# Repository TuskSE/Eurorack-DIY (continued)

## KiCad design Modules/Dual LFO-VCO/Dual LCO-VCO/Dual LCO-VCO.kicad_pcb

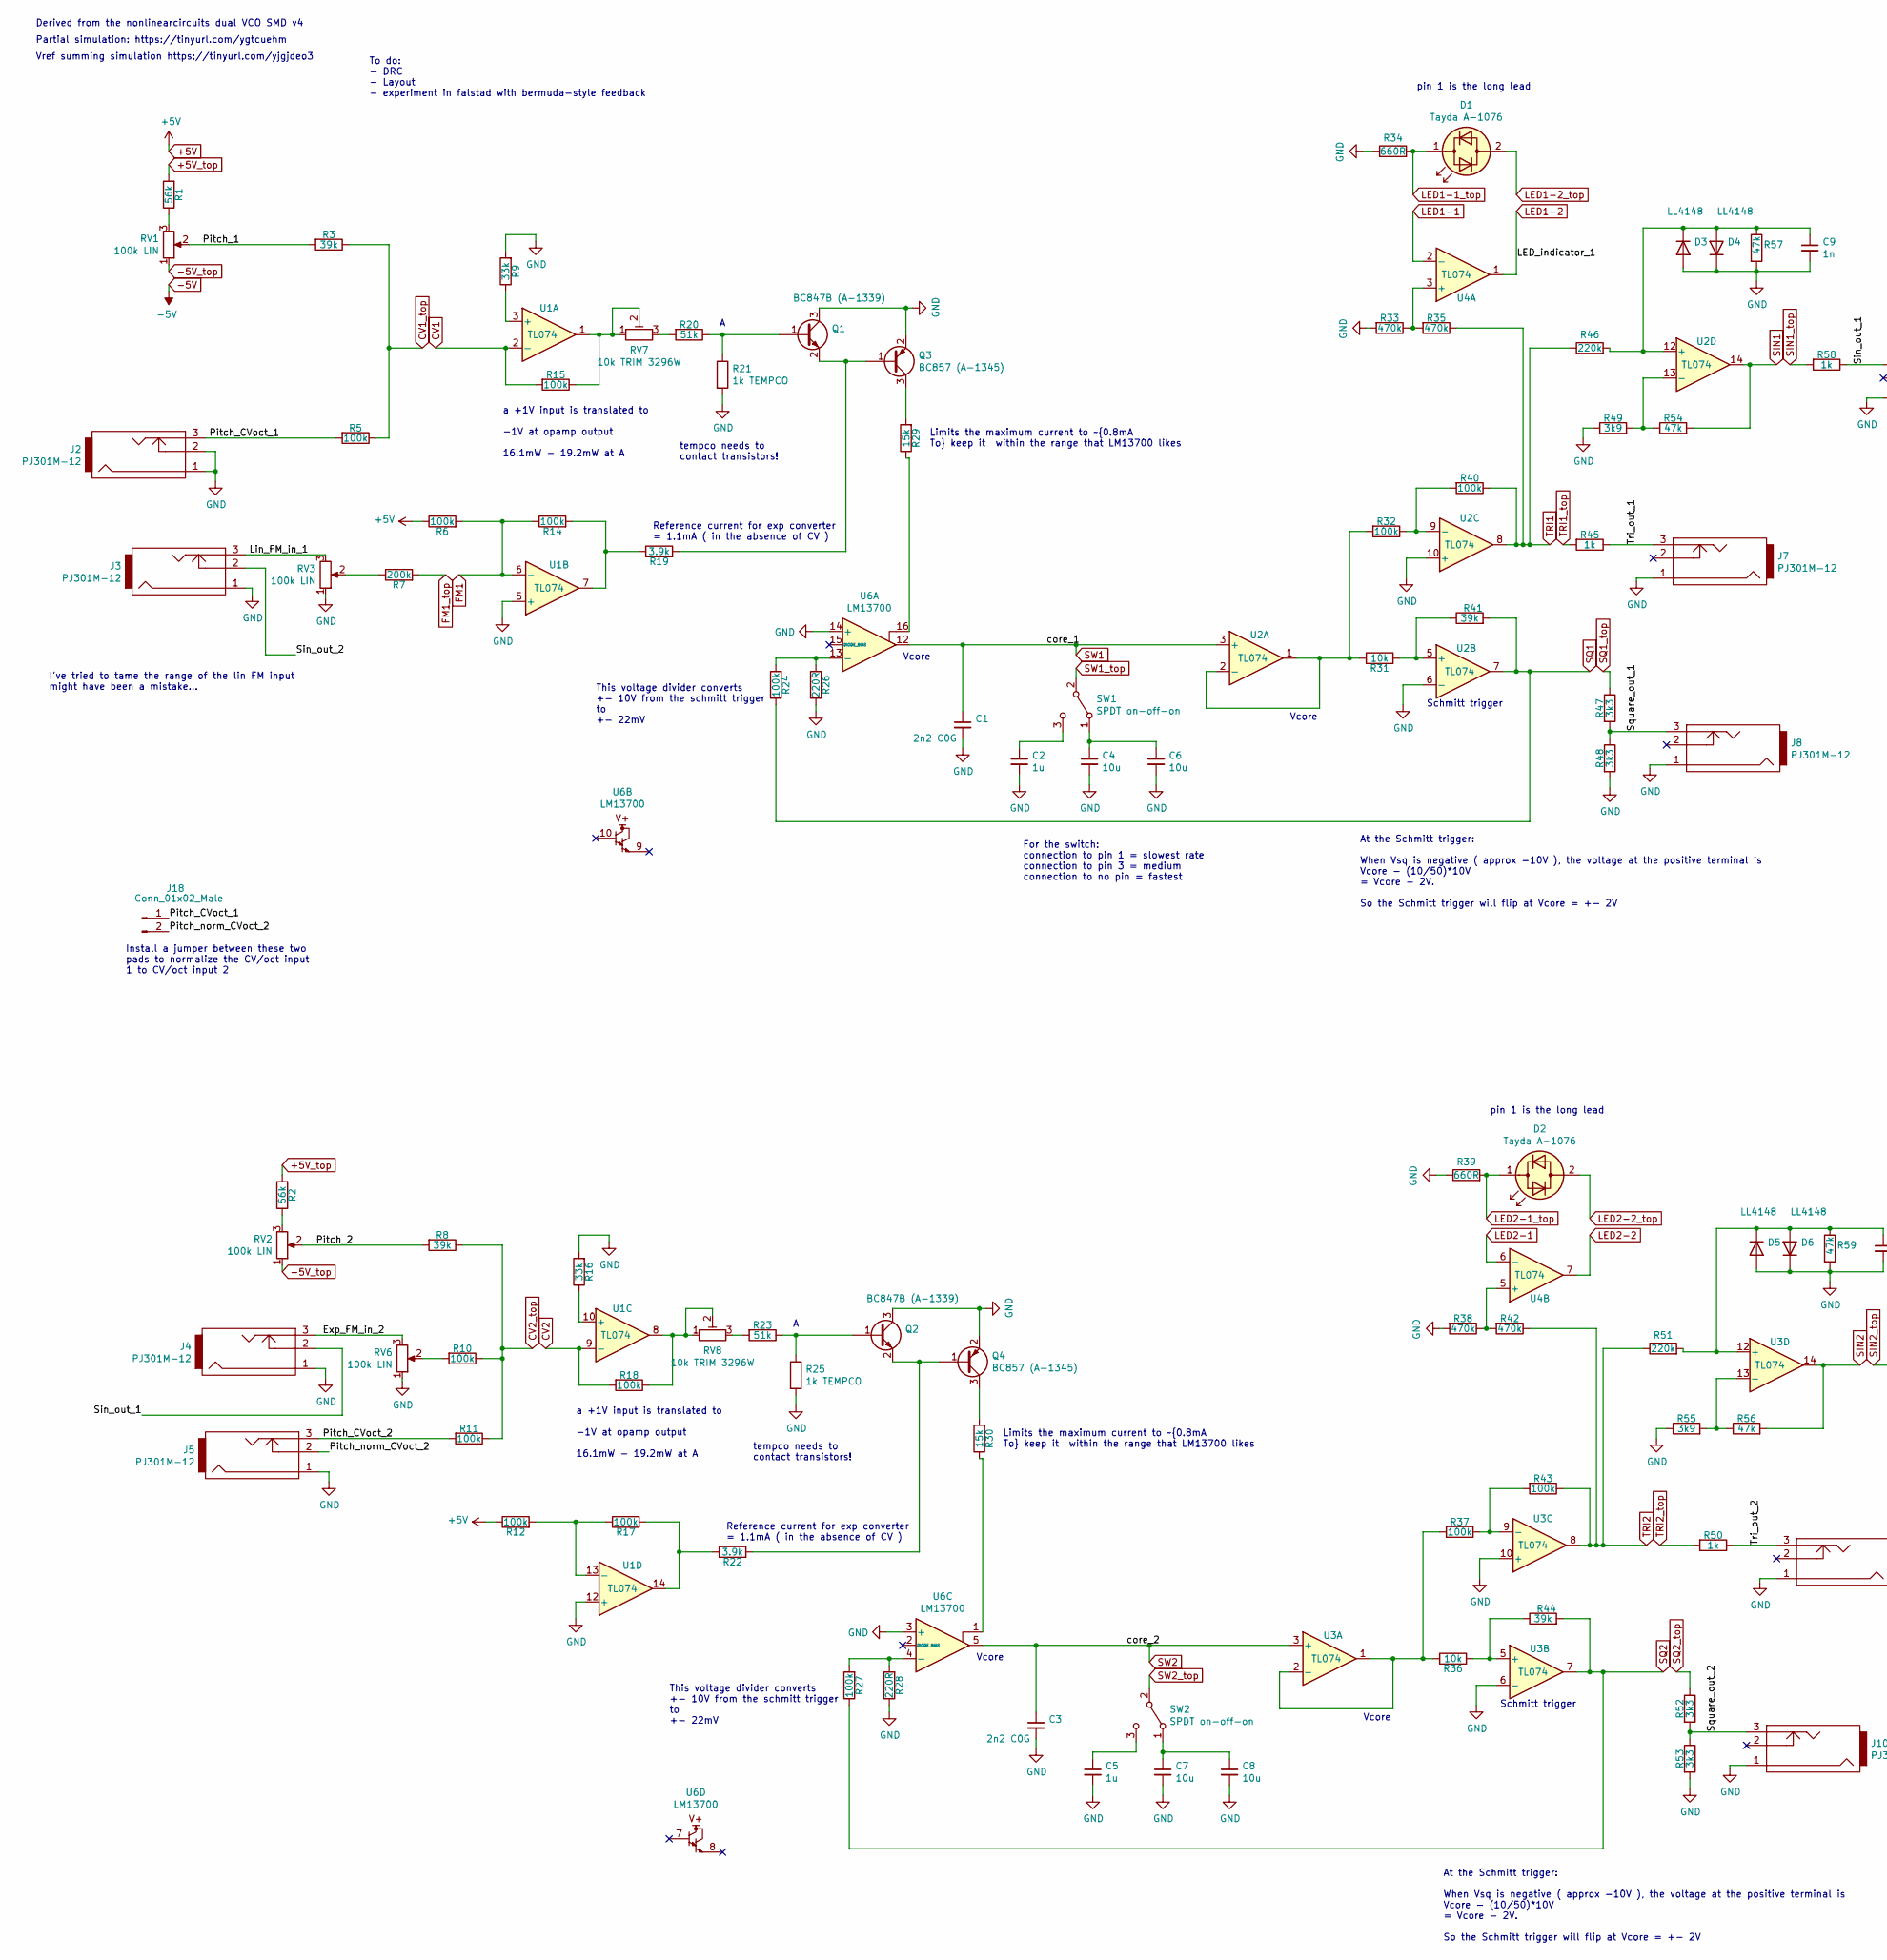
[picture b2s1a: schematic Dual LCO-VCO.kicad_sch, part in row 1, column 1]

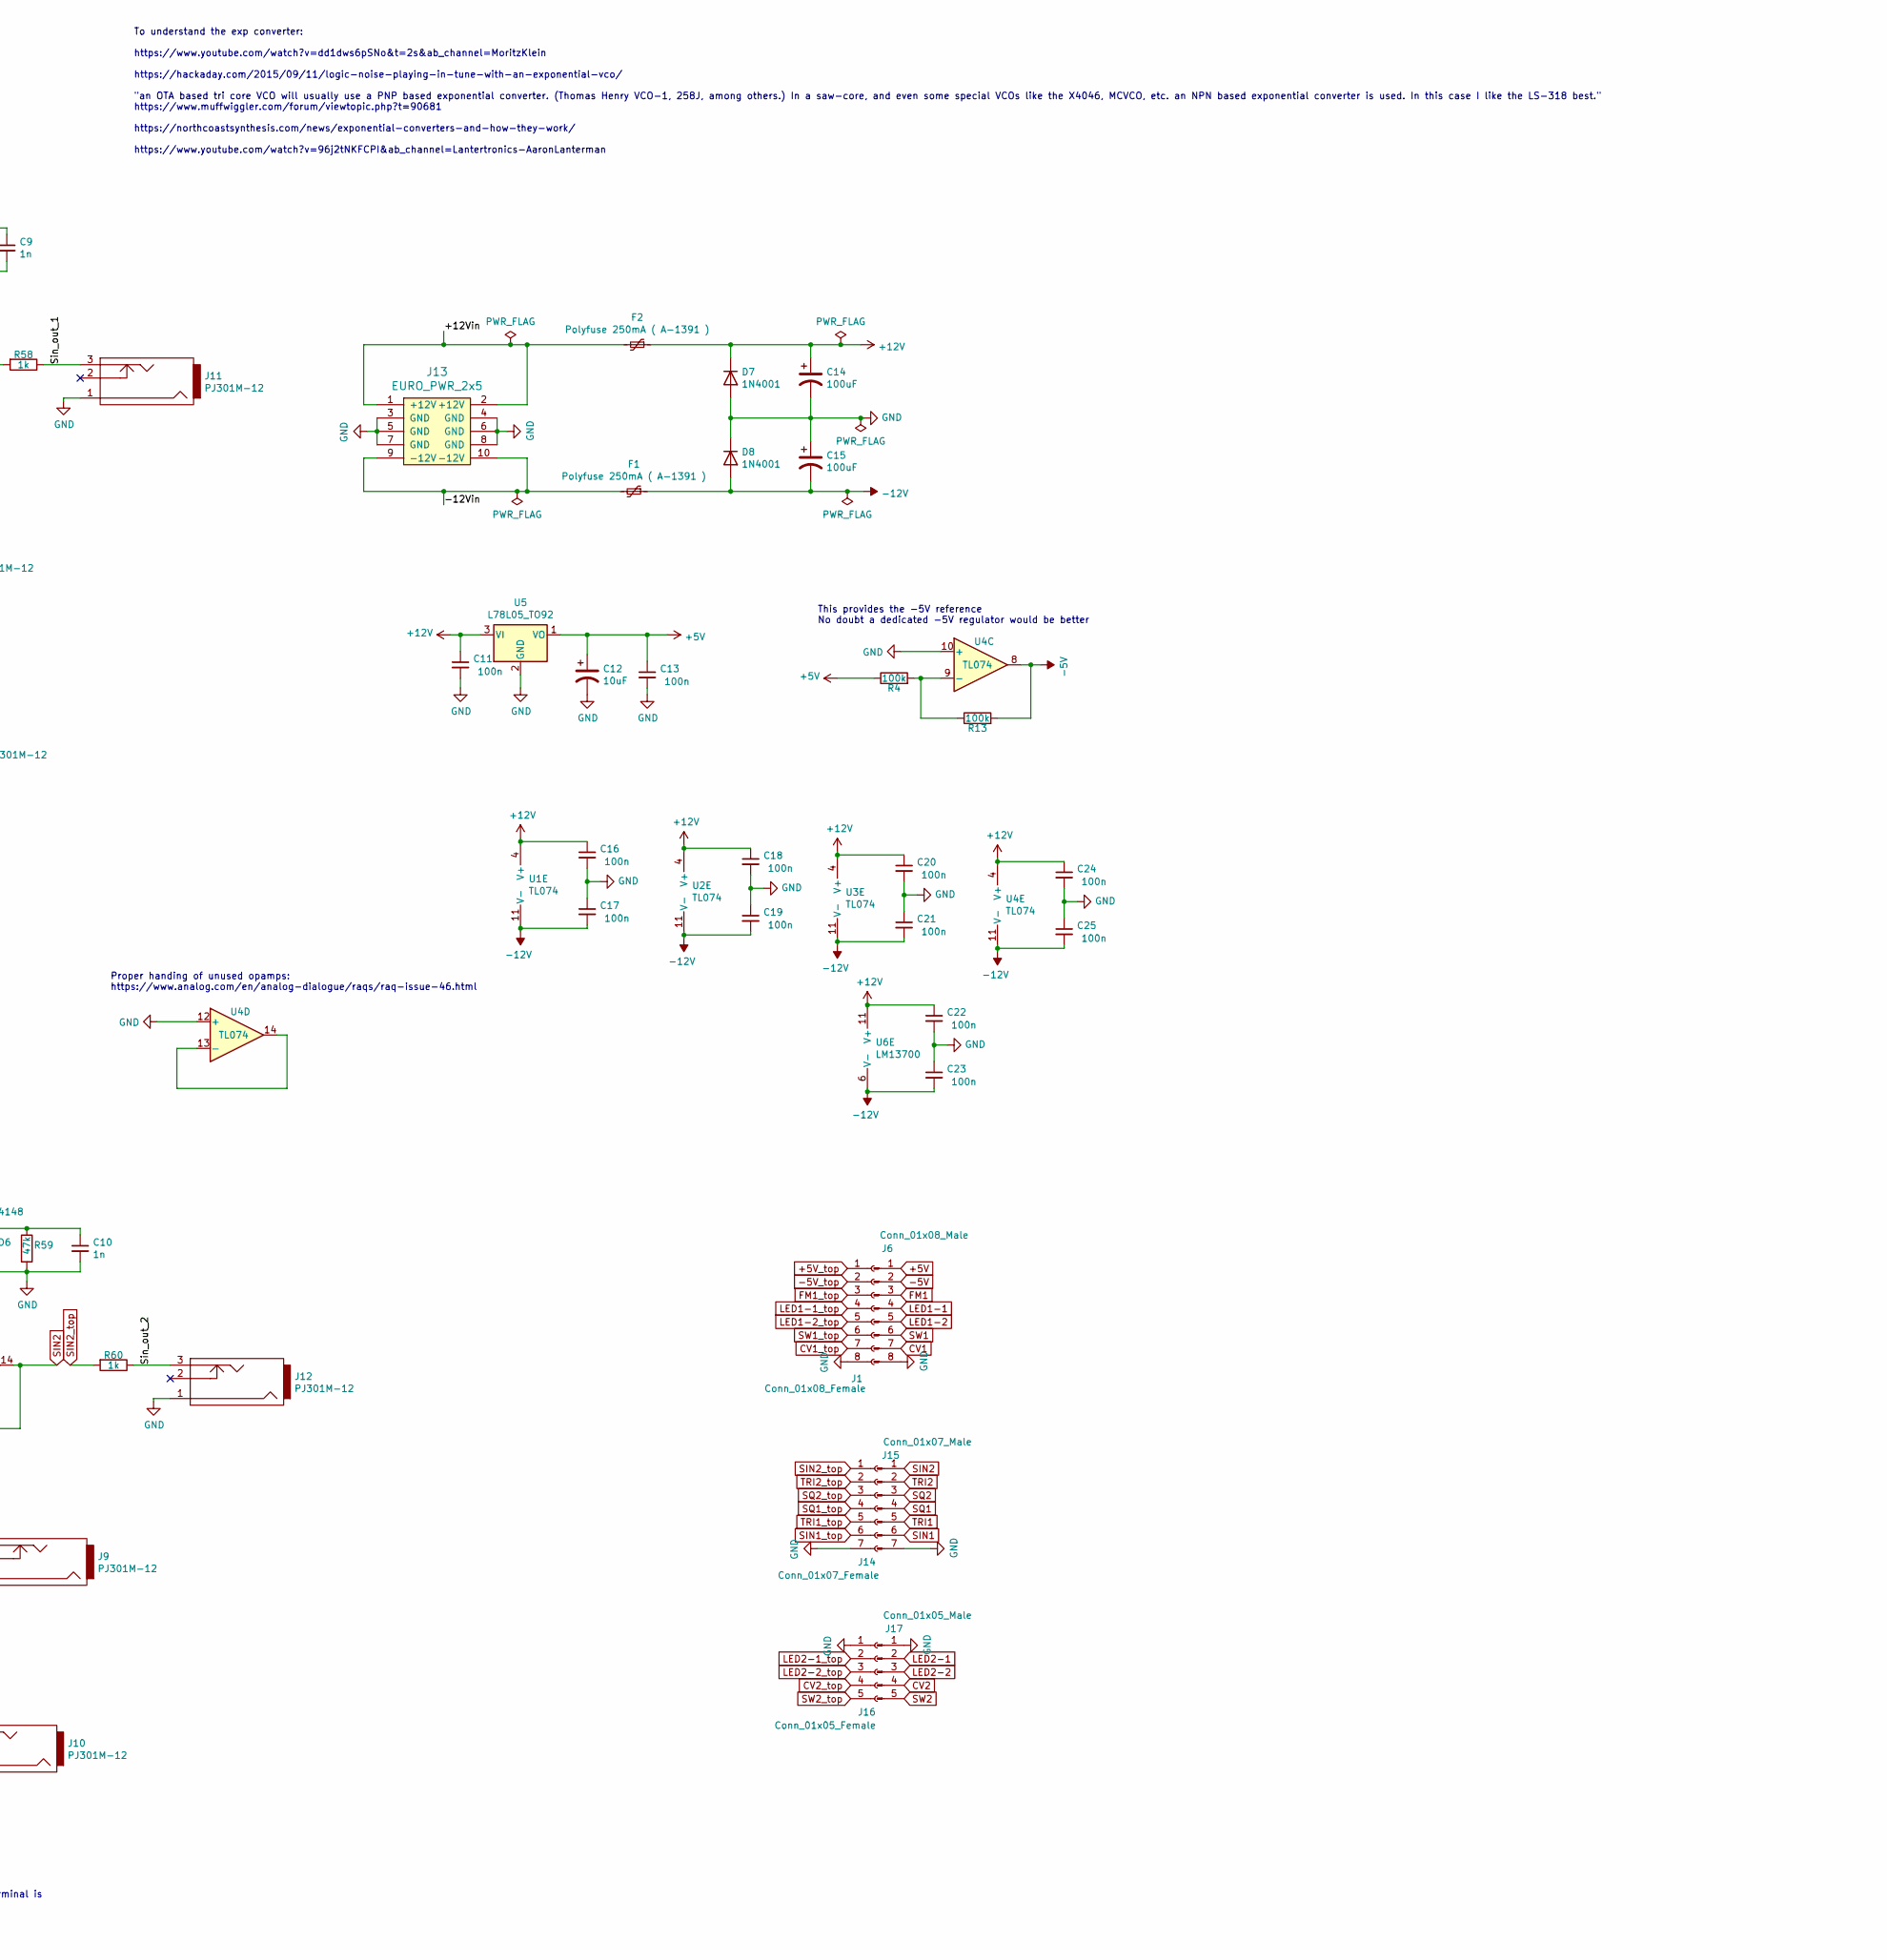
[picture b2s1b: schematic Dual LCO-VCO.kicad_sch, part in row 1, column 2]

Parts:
C1, C3: 2n2 C0G; C_0603_1608Metric_Pad1.05x0.95mm_HandSolder
C2, C5: 1u; C_0805_2012Metric_Pad1.15x1.40mm_HandSolder_smallText
C4, C6, C7, C8: 10u; C_0805_2012Metric_Pad1.15x1.40mm_HandSolder_smallText
C9, C10: 1n; C_0805_2012Metric_Pad1.15x1.40mm_HandSolder_SmallTxt
C11, C13, C16, C17, C18, C19, C20, C21, C22, C23, C24, C25: 100n; C_0805_2012Metric_Pad1.15x1.40mm_HandSolder_SmallTxt
C12: 10uF; CP_Radial_D6.3mm_P2.50mm
C14, C15: 100uF; CP_Radial_D6.3mm_P2.50mm
D1, D2: Tayda A-1076; LED3mm
D3, D4, D5, D6: LL4148; D_MiniMELF
D7, D8: 1N4001; D_DO-41_SOD81_P10.16mm_Horizontal
F1, F2: Polyfuse 250mA ( A-1391 ); C_Disc_D7.5mm_W2.5mm_P5.00mm
J1: Conn_01x08_Female; PinHeader_1x08_P2.54mm_Vertical
J2, J3, J4, J5, J7, J8, J9, J10, J11, J12: PJ301M-12; PJ301M-12_Compact
J6: Conn_01x08_Male; PinHeader_1x08_P2.54mm_Vertical
J13: EURO_PWR_2x5; Eurorack_power_header
J14: Conn_01x07_Female; PinHeader_1x07_P2.54mm_Vertical
J15: Conn_01x07_Male; PinHeader_1x07_P2.54mm_Vertical
J16: Conn_01x05_Female; PinHeader_1x05_P2.54mm_Vertical
J17: Conn_01x05_Male; PinHeader_1x05_P2.54mm_Vertical
J18: Conn_01x02_Male; PinHeader_1x02_P2.54mm_Vertical
Q1, Q2: BC847B (A-1339); SOT-23
Q3, Q4: BC857 (A-1345); SOT-23
R1, R2: 56k; R_0805_2012Metric_Pad1.15x1.40mm_HandSolder_smallText
R3, R8, R41, R44: 39k; R_0805_2012Metric_Pad1.15x1.40mm_HandSolder_smallText
R4, R5, R6, R10, R11, R12, R13, R14, R15, R17, R18, R24, R27, R32, R37, R40, R43: 100k; R_0805_2012Metric_Pad1.15x1.40mm_HandSolder_smallText
R7: 200k; R_0805_2012Metric_Pad1.15x1.40mm_HandSolder_smallText
R9, R16: 33k; R_0805_2012Metric_Pad1.15x1.40mm_HandSolder_smallText
R19, R22: 3.9k; R_0805_2012Metric_Pad1.15x1.40mm_HandSolder_smallText
R20, R23: 51k; R_0805_2012Metric_Pad1.15x1.40mm_HandSolder_smallText
R21, R25: 1k TEMPCO; R_Axial_DIN0414_L11.9mm_D4.5mm_P25.40mm_Horizontal
R26, R28: 220R; R_0805_2012Metric_Pad1.15x1.40mm_HandSolder_smallText
R29, R30: 15k; R_0805_2012Metric_Pad1.15x1.40mm_HandSolder_smallText
R31, R36: 10k; R_0805_2012Metric_Pad1.15x1.40mm_HandSolder_smallText
R33, R35, R38, R42: 470k; R_0805_2012Metric_Pad1.15x1.40mm_HandSolder_smallText
R34, R39: 660R; R_0805_2012Metric_Pad1.15x1.40mm_HandSolder_smallText
R45, R50, R58, R60: 1k; R_0805_2012Metric_Pad1.15x1.40mm_HandSolder_smallText
R46, R51: 220k; R_0805_2012Metric_Pad1.15x1.40mm_HandSolder_smallText
R47, R48, R52, R53: 3k3; R_0805_2012Metric_Pad1.15x1.40mm_HandSolder_smallText
R49, R55: 3k9; R_0805_2012Metric_Pad1.15x1.40mm_HandSolder_smallText
R54, R56, R57, R59: 47k; R_0805_2012Metric_Pad1.15x1.40mm_HandSolder_smallText
RV1, RV2, RV3, RV6: 100k LIN; Alpha9mmPot
RV7, RV8: 10k TRIM 3296W; Potentiometer_Bourns_3296W_Vertical
SW1, SW2: SPDT on-off-on; SPDT toggle on-off-on
U1, U2, U3, U4: TL074; SOIC-14_3.9x8.7mm_P1.27mm
U5: L78L05_TO92; TO-92_HandSolder
U6: LM13700; SOIC-16_3.9x9.9mm_P1.27mm

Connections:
+5V: C12.1, C13.1, J6.1, R4.1, R6.1, R12.1, U5.1 (VO)
+5V_top: J1.1, R1.2, R2.2
+12V: C11.1, C14.1, C16.1, C18.1, C20.1, C22.1, C24.1, D7.1 (K), F2.1, U1.4 (V+), U2.4 (V+), U3.4 (V+), U4.4 (V+), U5.3 (VI), U6.11 (V+)
-5V: J6.2, R13.2, U4.8
-5V_top: J1.2, RV1.1, RV2.1
-12V: C15.2, C17.2, C19.2, C21.2, C23.2, C25.2, D8.2 (A), F1.1, U1.11 (V-), U2.11 (V-), U3.11 (V-), U4.11 (V-), U6.6 (V-)
/+12Vin: F2.2, J13.1 (+12V), J13.2 (+12V)
/-12Vin: F1.2, J13.9 (-12V), J13.10 (-12V)
/Exp_FM_in_2: J4.3, RV6.3
/Lin_FM_in_1: J3.3, RV3.3
/Pitch_1: R3.2, RV1.2
/Pitch_2: R8.2, RV2.2
/Pitch_CVoct_1: J2.3, J18.1, R5.2
/Pitch_CVoct_2: J5.3, R11.2
/Pitch_norm_CVoct_2: J5.2, J18.2
/Sin_out_1: J4.2, J11.3, R58.1
/Sin_out_2: J3.2, J12.3, R60.1
/Square_out_1: J8.3, R47.2, R48.1
/Square_out_2: J10.3, R52.2, R53.1
/Tri_out_1: J7.3, R45.1
/Tri_out_2: J9.3, R50.1
CV1: J6.7, R15.2, U1.2 (-)
CV1_top: J1.7, R3.1, R5.1
CV2: J17.4, R18.2, U1.9 (-)
CV2_top: J16.4, R8.1, R10.1, R11.1
FM1: J6.3, R6.2, R14.1, U1.6 (-)
FM1_top: J1.3, R7.2
GND: C1.2, C2.2, C3.2, C4.2, C5.2, C6.2, C7.2, C8.2, C9.2, C10.2, C11.2, C12.2, C13.2, C14.2, C15.1, C16.2, C17.1, C18.2, C19.1, C20.2, C21.1, C22.2, C23.1, C24.2, C25.1, D3.2 (A), D4.1 (K), D5.2 (A), D6.1 (K), D7.2 (A), D8.1 (K), J1.8, J2.1, J2.2, J3.1, J4.1, J5.1, J6.8, J7.1, J8.1, J9.1, J10.1, J11.1, J12.1, J13.3 (GND), J13.4 (GND), J13.5 (GND), J13.6 (GND), J13.7 (GND), J13.8 (GND), J14.7, J15.7, J16.1, J17.1, Q1.3 (C), Q2.3 (C), Q3.2 (E), Q4.2 (E), R9.2, R16.2, R21.2, R25.2, R26.1, R28.1, R33.2, R34.1, R38.2, R39.1, R48.2, R49.1, R53.2, R55.1, R57.2, R59.2, RV3.1, RV6.1, U1.5 (+), U1.12 (+), U2.6 (-), U2.10 (+), U3.6 (-), U3.10 (+), U4.10 (+), U4.12 (+), U5.2 (GND), U6.3 (+), U6.14 (+)
LED1-1: J6.4, U4.2 (-)
LED1-1_top: D1.1 (KA), J1.4, R34.2
LED1-2: J6.5, U4.1
LED1-2_top: D1.2 (AK), J1.5
LED2-1: J17.2, U4.6 (-)
LED2-1_top: D2.1 (KA), J16.2, R39.2
LED2-2: J17.3, U4.7
LED2-2_top: D2.2 (AK), J16.3
unnamed: C2.1, SW1.3 (C)
unnamed: C4.1, C6.1, SW1.1 (A)
unnamed: C5.1, SW2.3 (C)
unnamed: C7.1, C8.1, SW2.1 (A)
unnamed: C9.1, D3.1 (K), D4.2 (A), R46.2, R57.1, U2.12 (+)
unnamed: C10.1, D5.1 (K), D6.2 (A), R51.2, R59.1, U3.12 (+)
unnamed: Q1.1 (B), R20.1, R21.1
unnamed: Q1.2 (E), Q3.1 (B), R19.2
unnamed: Q2.1 (B), R23.1, R25.1
unnamed: Q2.2 (E), Q4.1 (B), R22.2
unnamed: Q3.3 (C), R29.2
unnamed: Q4.3 (C), R30.2
unnamed: R1.1, RV1.3
unnamed: R2.1, RV2.3
unnamed: R7.1, RV3.2
unnamed: R9.1, U1.3 (+)
unnamed: R10.2, RV6.2
unnamed: R12.2, R17.1, U1.13 (-)
unnamed: R4.2, R13.1, U4.9 (-)
unnamed: R14.2, R19.1, U1.7
unnamed: R15.1, RV7.1, RV7.2, U1.1
unnamed: R16.1, U1.10 (+)
unnamed: R17.2, R22.1, U1.14
unnamed: R18.1, RV8.1, RV8.2, U1.8
unnamed: R20.2, RV7.3
unnamed: R23.2, RV8.3
unnamed: R24.2, R26.2, U6.13 (-)
unnamed: R27.2, R28.2, U6.4 (-)
unnamed: R29.1, U6.16
unnamed: R30.1, U6.1
unnamed: R31.1, R32.2, U2.1, U2.2 (-)
unnamed: R31.2, R41.1, U2.5 (+)
unnamed: R32.1, R40.2, U2.9 (-)
unnamed: R33.1, R35.2, U4.3 (+)
unnamed: R36.1, R37.2, U3.1, U3.2 (-)
unnamed: R36.2, R44.1, U3.5 (+)
unnamed: R37.1, R43.2, U3.9 (-)
unnamed: R38.1, R42.2, U4.5 (+)
unnamed: R49.2, R54.1, U2.13 (-)
unnamed: R55.2, R56.1, U3.13 (-)
unnamed: U4.13 (-), U4.14
SIN1: J15.6, R54.2, U2.14
SIN1_top: J14.6, R58.2
SIN2: J15.1, R56.2, U3.14
SIN2_top: J14.1, R60.2
SQ1: J15.4, R24.1, R41.2, U2.7
SQ1_top: J14.4, R47.1
SQ2: J15.3, R27.1, R44.2, U3.7
SQ2_top: J14.3, R52.1
SW1: C1.1, J6.6, U2.3 (+), U6.12
SW1_top: J1.6, SW1.2 (B)
SW2: C3.1, J17.5, U3.3 (+), U6.5
SW2_top: J16.5, SW2.2 (B)
TRI1: J15.5, R35.1, R40.1, R46.1, U2.8
TRI1_top: J14.5, R45.2
TRI2: J15.2, R42.1, R43.1, R51.1, U3.8
TRI2_top: J14.2, R50.2

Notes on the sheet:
This voltage divider converts +- 10V from the schmitt trigger to +- 22mV
pin 1 is the long lead
a +1V input is translated to -1V at opamp output 16.1mW - 19.2mW at A
Schmitt trigger
This provides the -5V reference No doubt a dedicated -5V regulator would be better
Limits the maximum current to ~{0.8mA To} keep it within the range that LM13700 likes
For the switch: connection to pin 1 = slowest rate connection to pin 3 = medium connection to no pin = fastest
To do: - DRC - Layout - experiment in falstad with bermuda-style feedback
I've tried to tame the range of the lin FM input might have been a mistake...
Reference current for exp converter = 1.1mA ( in the absence of CV )
Proper handing of unused opamps: https://www.analog.com/en/analog-dialogue/raqs/raq-issue-46.html
At the Schmitt trigger: When Vsq is negative ( approx -10V ), the voltage at the positive terminal is Vcore - (10/50)*10V = Vcore - 2V. So the Schmitt trigger will flip at Vcore = +- 2V
Vcore
Vref summing simulation https://tinyurl.com/yjgjdeo3
Partial simulation: https://tinyurl.com/ygtcuehm
Derived from the nonlinearcircuits dual VCO SMD v4
tempco needs to contact transistors!
To understand the exp converter: https://www.youtube.com/watch?v=dd1dws6pSNo&t=2s&ab_channel=MoritzKlein https://hackaday.com/2015/09/11/logic-noise-playing-in-tune-with-an-exponential-vco/ "an OTA based tri core VCO will usually use a PNP based exponential converter. (Thomas Henry VCO-1, 258J, amo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
Install a jumper between these two pads to normalize the CV/oct input 1 to CV/oct input 2

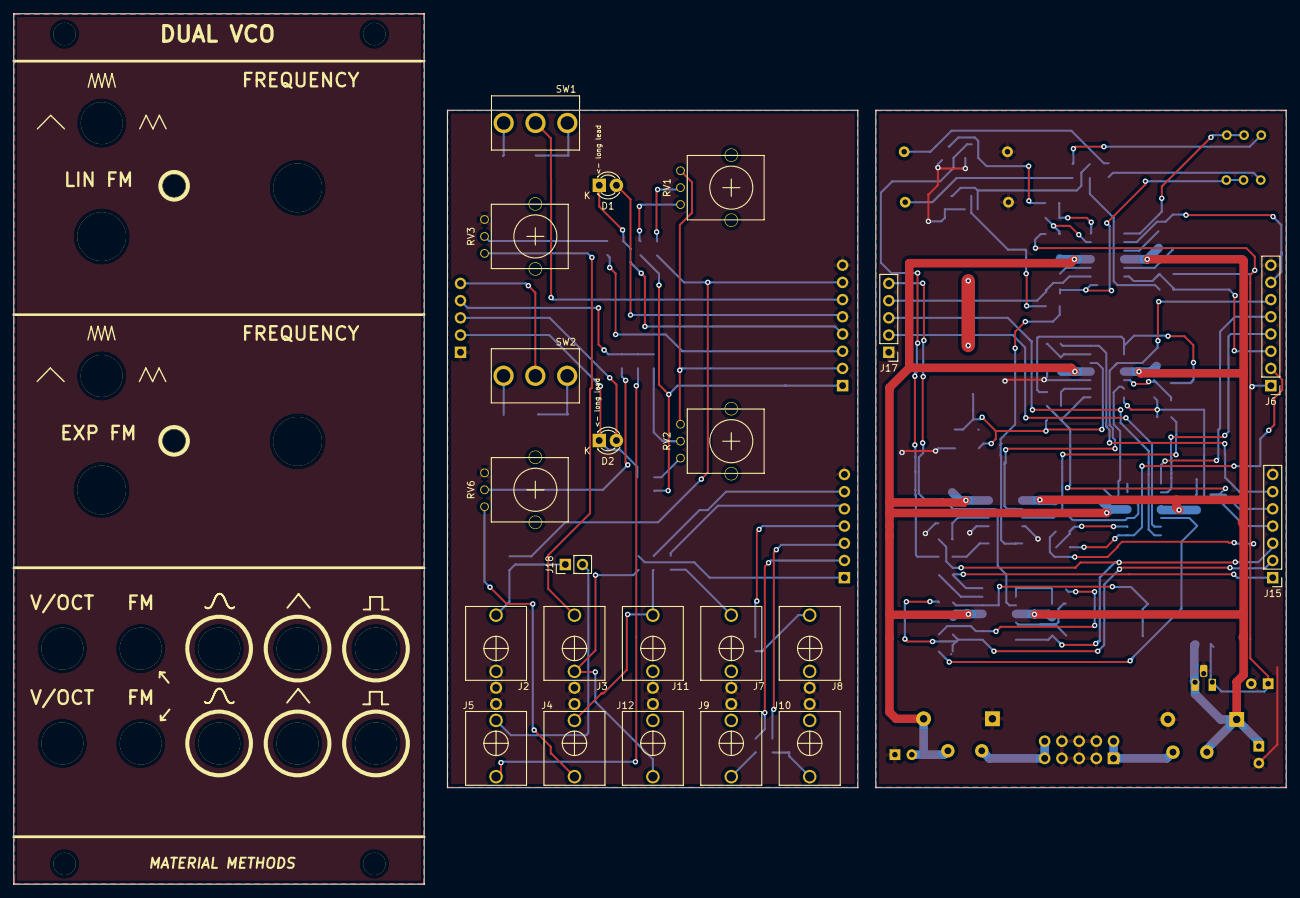
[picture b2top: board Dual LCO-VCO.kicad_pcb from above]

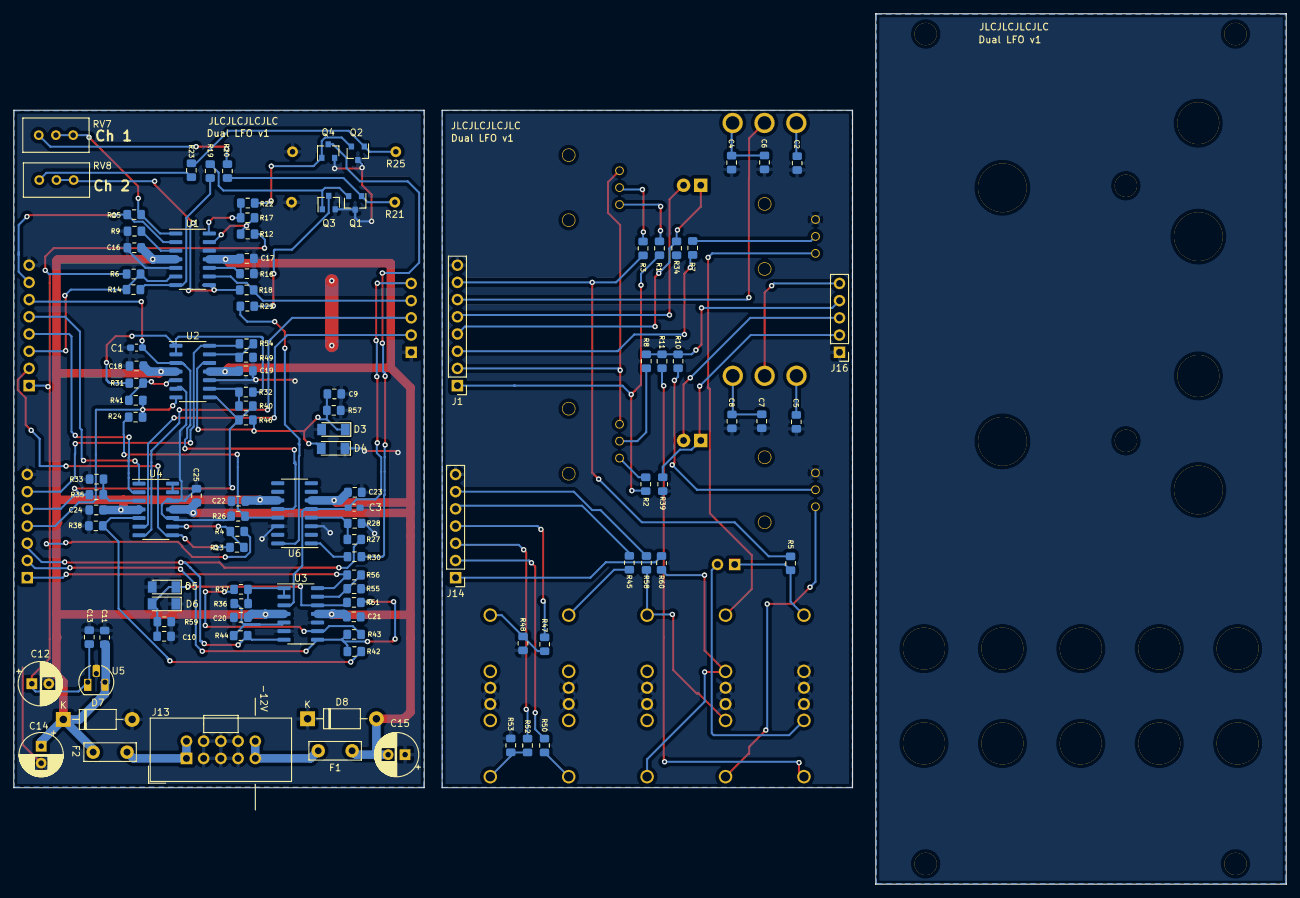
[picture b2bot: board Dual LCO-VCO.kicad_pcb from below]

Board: 2 copper layers, 187.8 x 128.5 mm, 131 parts (109 on the bottom side), 93 nets.
